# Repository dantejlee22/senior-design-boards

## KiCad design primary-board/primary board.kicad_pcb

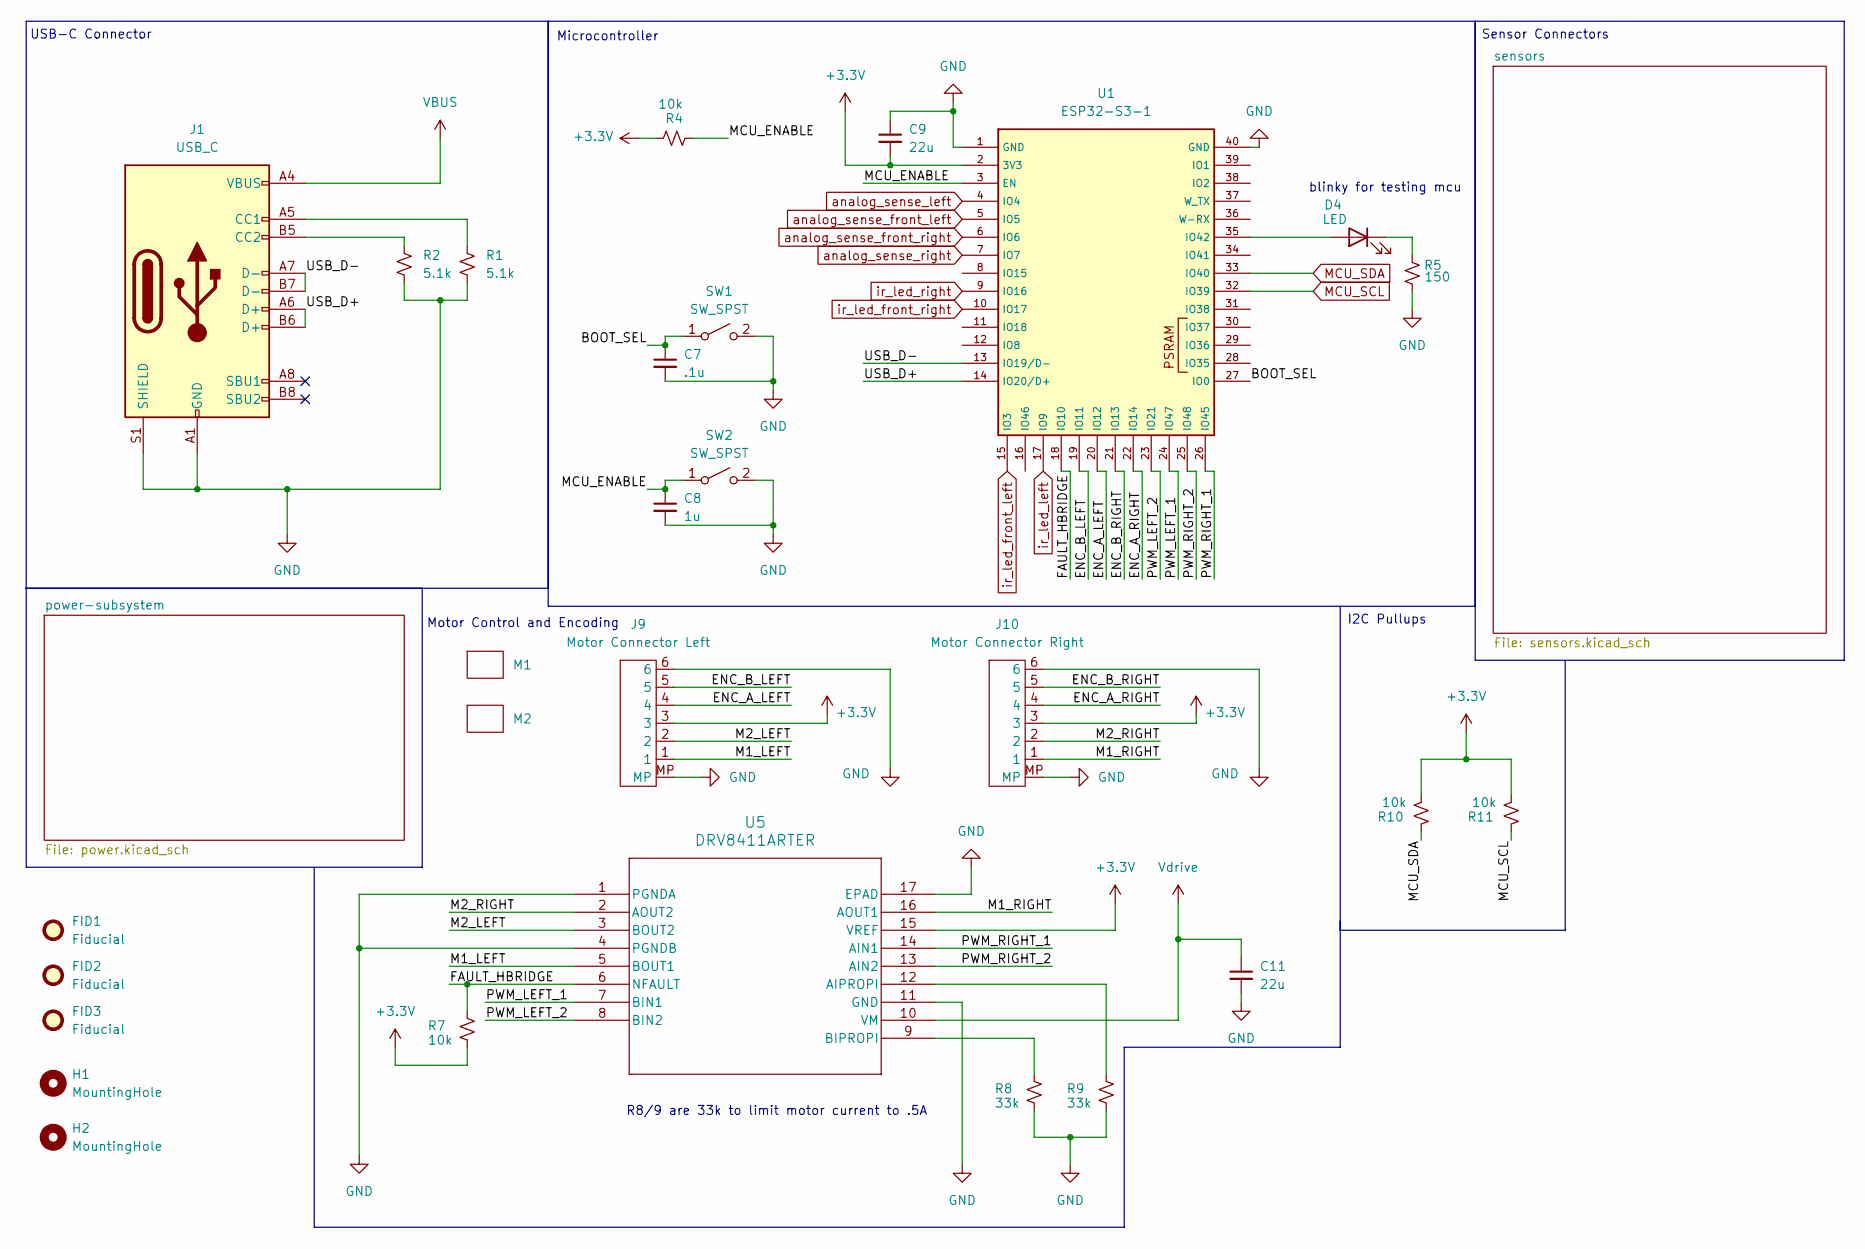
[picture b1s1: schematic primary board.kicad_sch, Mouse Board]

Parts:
C7: .1u; C_0603_1608Metric
C8: 1u; C_0603_1608Metric
C9, C11: 22u; C_0805_2012Metric
D4: LED; LED_0603_1608Metric
FID1, FID2, FID3: Fiducial; Fiducial_0.5mm_Mask1mm
H1, H2: MountingHole; MountingHole_2.2mm_M2
J1: USB_C; USB_C_Receptacle_GCT_USB4105-xx-A_16P_TopMnt_Horizontal
J9: Motor Connector Left; JST_SH_6_V
J10: Motor Connector Right; JST_SH_6_V
M1, M2: gearmotorenc
R1, R2: 5.1k; R_0603_1608Metric
R4, R7, R10, R11: 10k; R_0603_1608Metric
R5: 150; R_0603_1608Metric
R8, R9: 33k; R_0603_1608Metric_Pad0.98x0.95mm_HandSolder
SW1, SW2: SW_SPST; SW_SPST_Omron_B3FS-101xP
U1: ESP32-S3-1; ESP32-S3-1-WROOM_1
U5: DRV8411ARTER; WQFN16_RTE_TEX

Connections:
+3.3V: C9.2, J9.3, J10.3, R4.2, R7.2, R10.2, R11.2, U1.2 (3V3), U5.15 (VREF); also elsewhere on the board
/BOOT_SEL: C7.1, SW1.1 (A), U1.27 (IO0)
/ENC_A_LEFT: J9.4, U1.20 (IO12)
/ENC_A_RIGHT: J10.4, U1.22 (IO14)
/ENC_B_LEFT: J9.5, U1.19 (IO11)
/ENC_B_RIGHT: J10.5, U1.21 (IO13)
/FAULT_HBRIDGE: R7.1, U1.18 (IO10), U5.6 (NFAULT)
/M1_LEFT: J9.1, U5.5 (BOUT1)
/M1_RIGHT: J10.1, U5.16 (AOUT1)
/M2_LEFT: J9.2, U5.3 (BOUT2)
/M2_RIGHT: J10.2, U5.2 (AOUT2)
/MCU_ENABLE: C8.1, R4.1, SW2.1 (A), U1.3 (EN)
/PWM_LEFT_1: U1.24 (IO47), U5.7 (BIN1)
/PWM_LEFT_2: U1.23 (IO21), U5.8 (BIN2)
/PWM_RIGHT_1: U1.26 (IO45), U5.14 (AIN1)
/PWM_RIGHT_2: U1.25 (IO48), U5.13 (AIN2)
/USB_D+: J1.A6 (D+), J1.B6 (D+), U1.14 (IO20/D+)
/USB_D-: J1.A7 (D-), J1.B7 (D-), U1.13 (IO19/D-)
GND: C7.2, C8.2, C9.1, C11.2, J1.A1 (GND), J1.A12 (GND), J1.B1 (GND), J1.B12 (GND), J1.S1 (SHIELD), J9.6, J9.MP, J10.6, J10.MP, R1.1, R2.1, R5.1, R8.2, R9.2, SW1.2 (B), SW2.2 (B), U1.1 (GND), U1.40 (GND), U1.41 (GND__1), U5.1 (PGNDA), U5.4 (PGNDB), U5.11 (GND), U5.17 (EPAD); also elsewhere on the board
MCU_SCL: R11.1, U1.32 (IO39); also elsewhere on the board
MCU_SDA: R10.1, U1.33 (IO40); also elsewhere on the board
unnamed: D4.2 (A), U1.35 (IO42)
unnamed: D4.1 (K), R5.2
unnamed: J1.A5 (CC1), R1.2
unnamed: J1.B5 (CC2), R2.2
unnamed: R9.1, U5.12 (AIPROPI)
unnamed: R8.1, U5.9 (BIPROPI)
VBUS: J1.A4 (VBUS), J1.A9 (VBUS), J1.B4 (VBUS), J1.B9 (VBUS); also elsewhere on the board
Vdrive: C11.1, U5.10 (VM)
analog_sense_front_left: U1.5 (IO5); also elsewhere on the board
analog_sense_front_right: U1.6 (IO6); also elsewhere on the board
analog_sense_left: U1.4 (IO4); also elsewhere on the board
analog_sense_right: U1.7 (IO7); also elsewhere on the board
ir_led_front_left: U1.15 (IO3); also elsewhere on the board
ir_led_front_right: U1.10 (IO17); also elsewhere on the board
ir_led_left: U1.17 (IO9); also elsewhere on the board
ir_led_right: U1.9 (IO16); also elsewhere on the board

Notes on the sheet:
blinky for testing mcu
I2C Pullups
Motor Control and Encoding
USB-C Connector
Sensor Connectors
Microcontroller
R8/9 are 33k to limit motor current to .5A

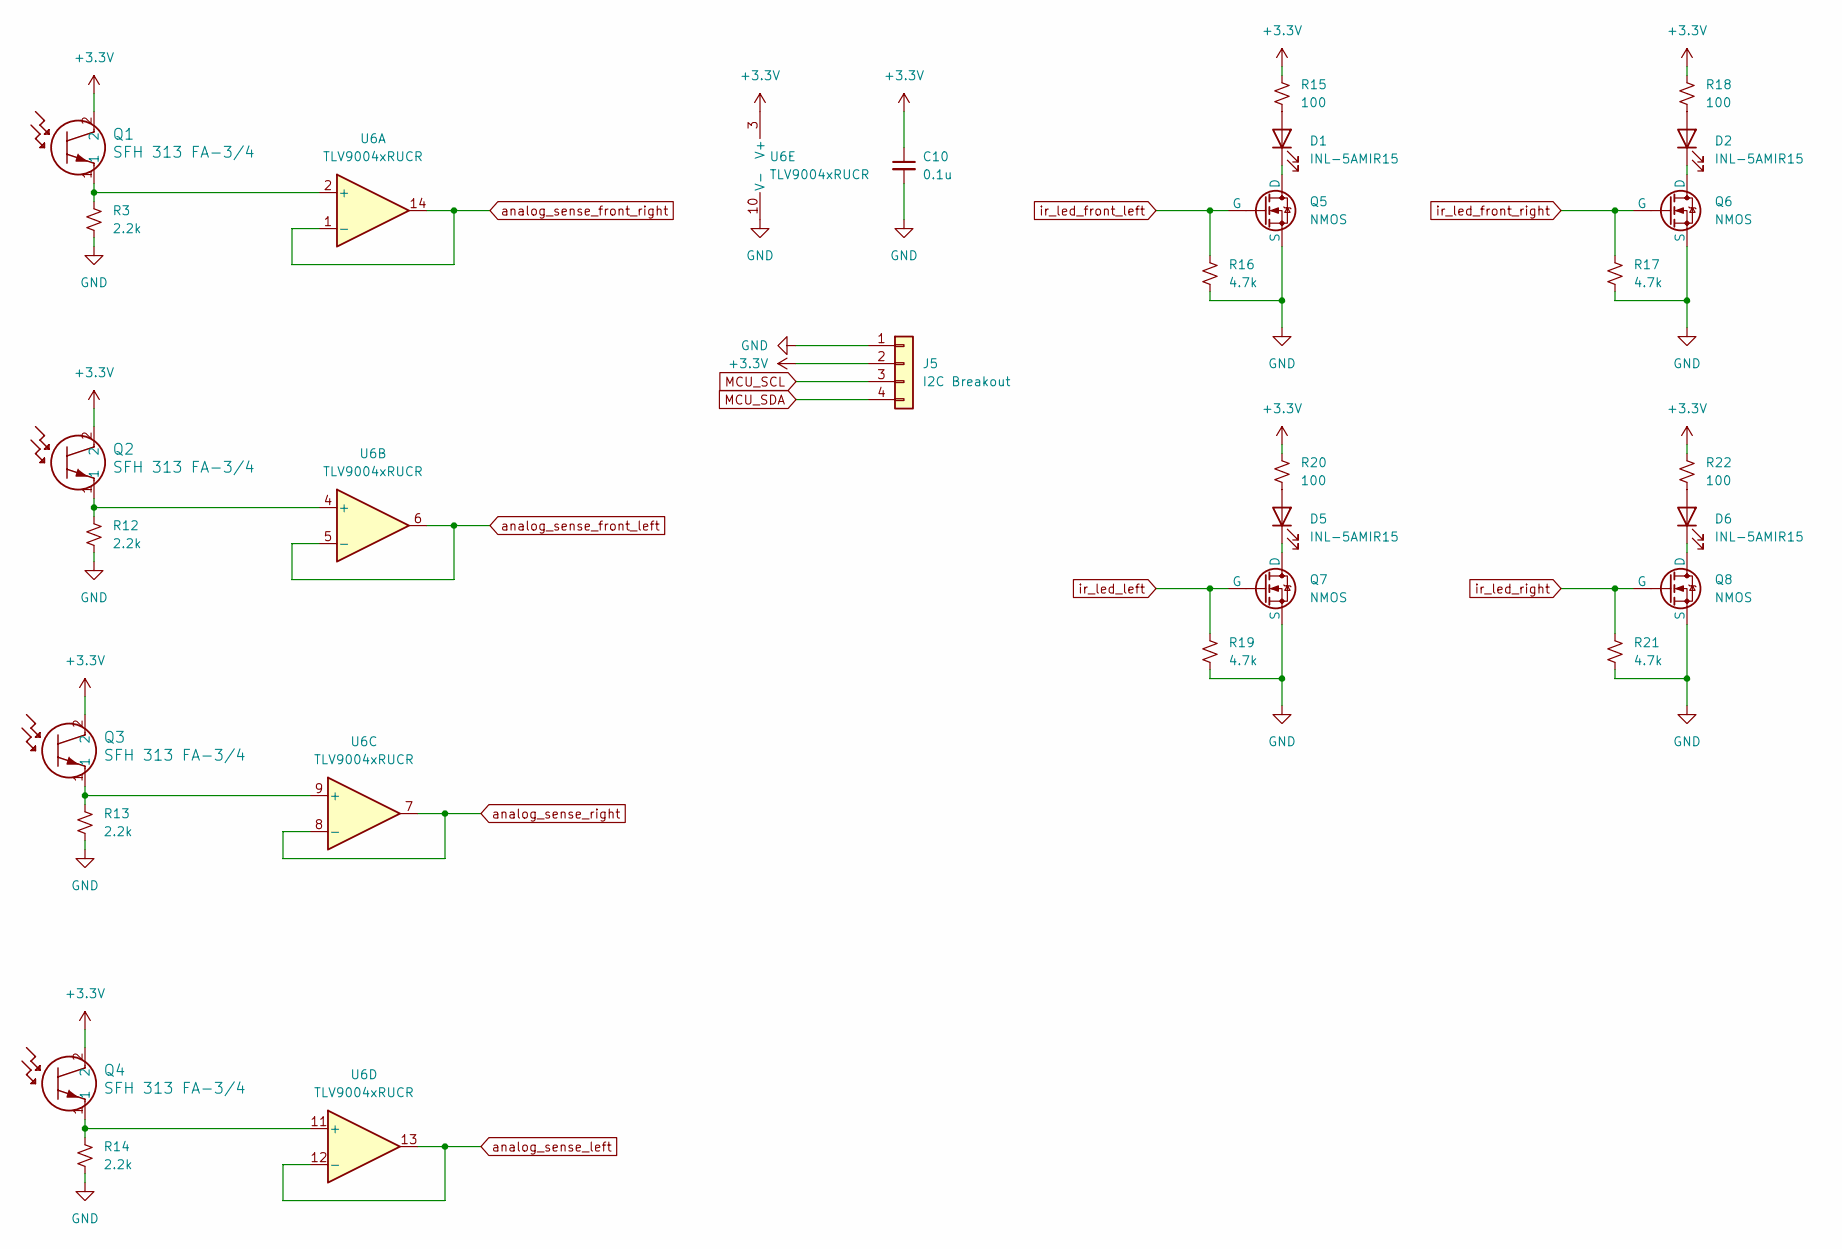
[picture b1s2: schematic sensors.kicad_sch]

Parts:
C10: 0.1u; C_0603_1608Metric
D1, D2, D5, D6: INL-5AMIR15; LED_D5.0mm_IRGrey
J5: I2C Breakout; PinSocket_1x04_P2.54mm_Vertical
Q1, Q2, Q3, Q4: SFH 313 FA-3/4; LED_D5.0mm_IRGrey
Q5, Q6, Q7, Q8: NMOS; SOT-23-3
R3, R12, R13, R14: 2.2k; R_0603_1608Metric
R15, R18, R20, R22: 100; R_0603_1608Metric
R16, R17, R19, R21: 4.7k; R_0603_1608Metric
U6: TLV9004xRUCR; Texas_S-PX2QFN-14

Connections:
+3.3V: C10.1, J5.2, Q1.2, Q2.2, Q3.2, Q4.2, R15.1, R18.1, R20.1, R22.1, U6.3 (V+); also elsewhere on the board
GND: C10.2, J5.1, Q5.3 (S), Q6.3 (S), Q7.3 (S), Q8.3 (S), R3.2, R12.2, R13.2, R14.2, R16.2, R17.2, R19.2, R21.2, U6.10 (V-); also elsewhere on the board
MCU_SCL: J5.3; also elsewhere on the board
MCU_SDA: J5.4; also elsewhere on the board
unnamed: D1.2 (A), R15.2
unnamed: D1.1 (K), Q5.1 (D)
unnamed: D2.2 (A), R18.2
unnamed: D2.1 (K), Q6.1 (D)
unnamed: D5.2 (A), R20.2
unnamed: D5.1 (K), Q7.1 (D)
unnamed: D6.2 (A), R22.2
unnamed: D6.1 (K), Q8.1 (D)
unnamed: Q1.1, R3.1, U6.2 (+)
unnamed: Q2.1, R12.1, U6.4 (+)
unnamed: Q3.1, R13.1, U6.9 (+)
unnamed: Q4.1, R14.1, U6.11 (+)
analog_sense_front_left: U6.5 (-), U6.6; also elsewhere on the board
analog_sense_front_right: U6.1 (-), U6.14; also elsewhere on the board
analog_sense_left: U6.12 (-), U6.13; also elsewhere on the board
analog_sense_right: U6.7, U6.8 (-); also elsewhere on the board
ir_led_front_left: Q5.2 (G), R16.1; also elsewhere on the board
ir_led_front_right: Q6.2 (G), R17.1; also elsewhere on the board
ir_led_left: Q7.2 (G), R19.1; also elsewhere on the board
ir_led_right: Q8.2 (G), R21.1; also elsewhere on the board

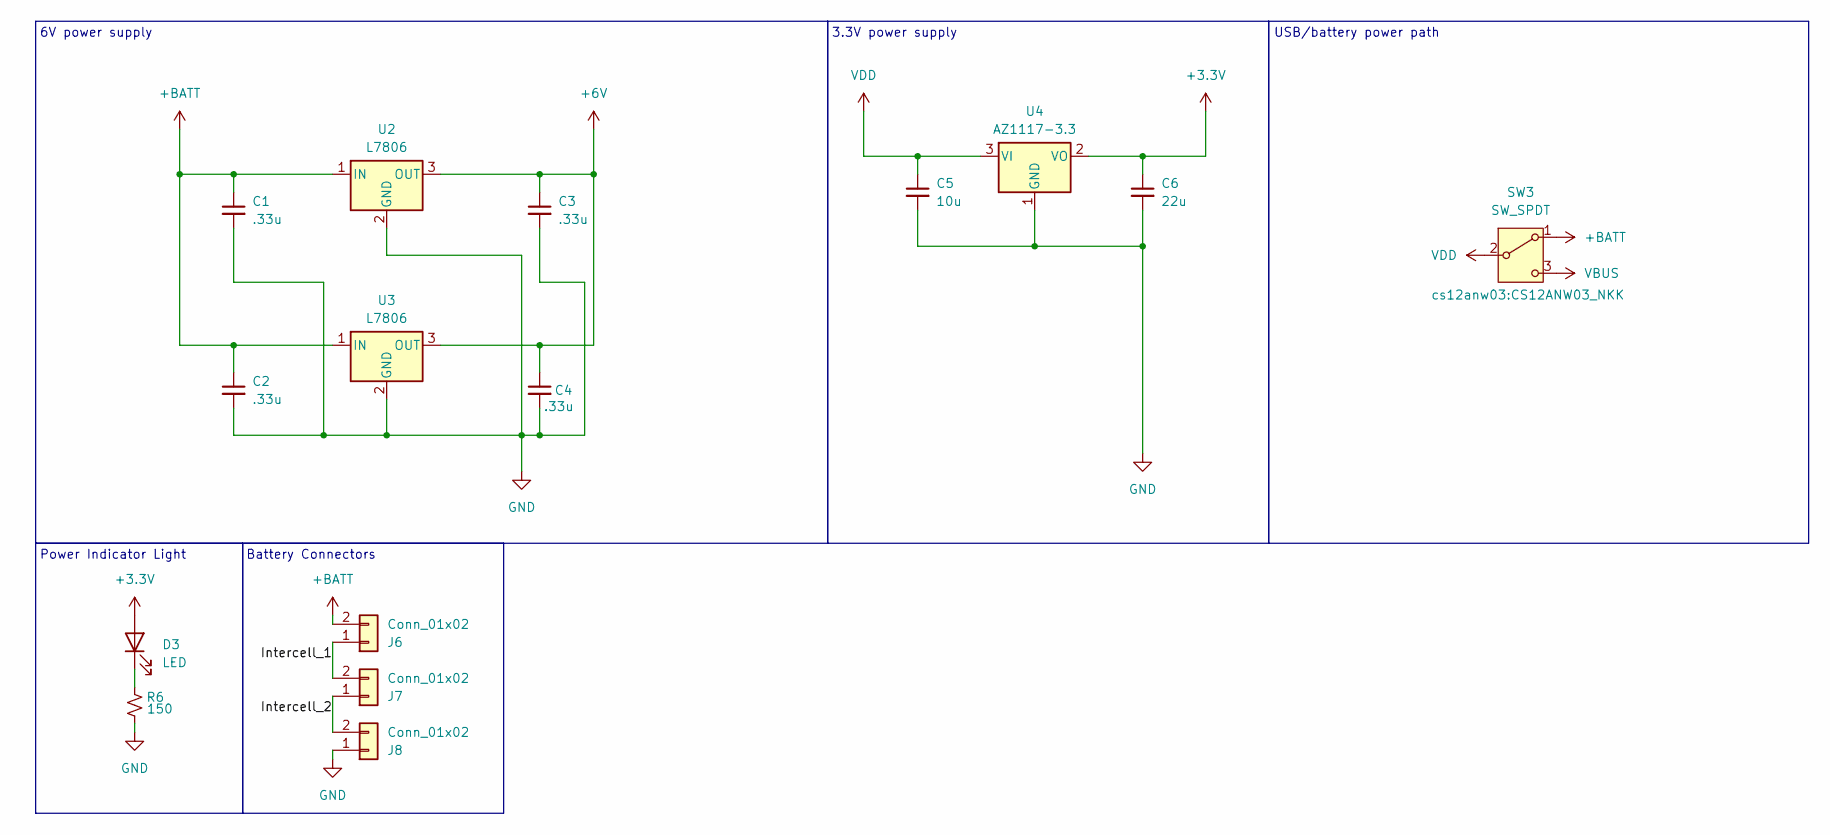
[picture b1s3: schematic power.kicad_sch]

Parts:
C1, C2, C3, C4: .33u; C_0603_1608Metric
C5: 10u; C_0805_2012Metric
C6: 22u; C_0805_2012Metric
D3: LED; LED_0603_1608Metric
J6, J7, J8: Conn_01x02; JST_PH_B2B-PH-K_1x02_P2.00mm_Vertical
R6: 150; R_0603_1608Metric
SW3: SW_SPDT; CS12ANW03_NKK
U2, U3: L7806; TO-263-2
U4: AZ1117-3.3; SOT-223-3_TabPin2

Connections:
+3.3V: C6.1, D3.2 (A), U4.2 (VO); also elsewhere on the board
+6V: C3.1, C4.1, U2.3 (OUT), U3.3 (OUT)
+BATT: C1.1, C2.1, J6.2, SW3.1 (A), U2.1 (IN), U3.1 (IN)
/power-subsystem/Intercell_1: J6.1, J7.2
/power-subsystem/Intercell_2: J7.1, J8.2
GND: C1.2, C2.2, C3.2, C4.2, C5.2, C6.2, J8.1, R6.1, U2.2 (GND), U3.2 (GND), U4.1 (GND); also elsewhere on the board
unnamed: D3.1 (K), R6.2
VBUS: SW3.3 (C); also elsewhere on the board
VDD: C5.1, SW3.2 (B), U4.3 (VI)

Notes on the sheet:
3.3V power supply
USB/battery power path
Battery Connectors
Power Indicator Light
6V power supply

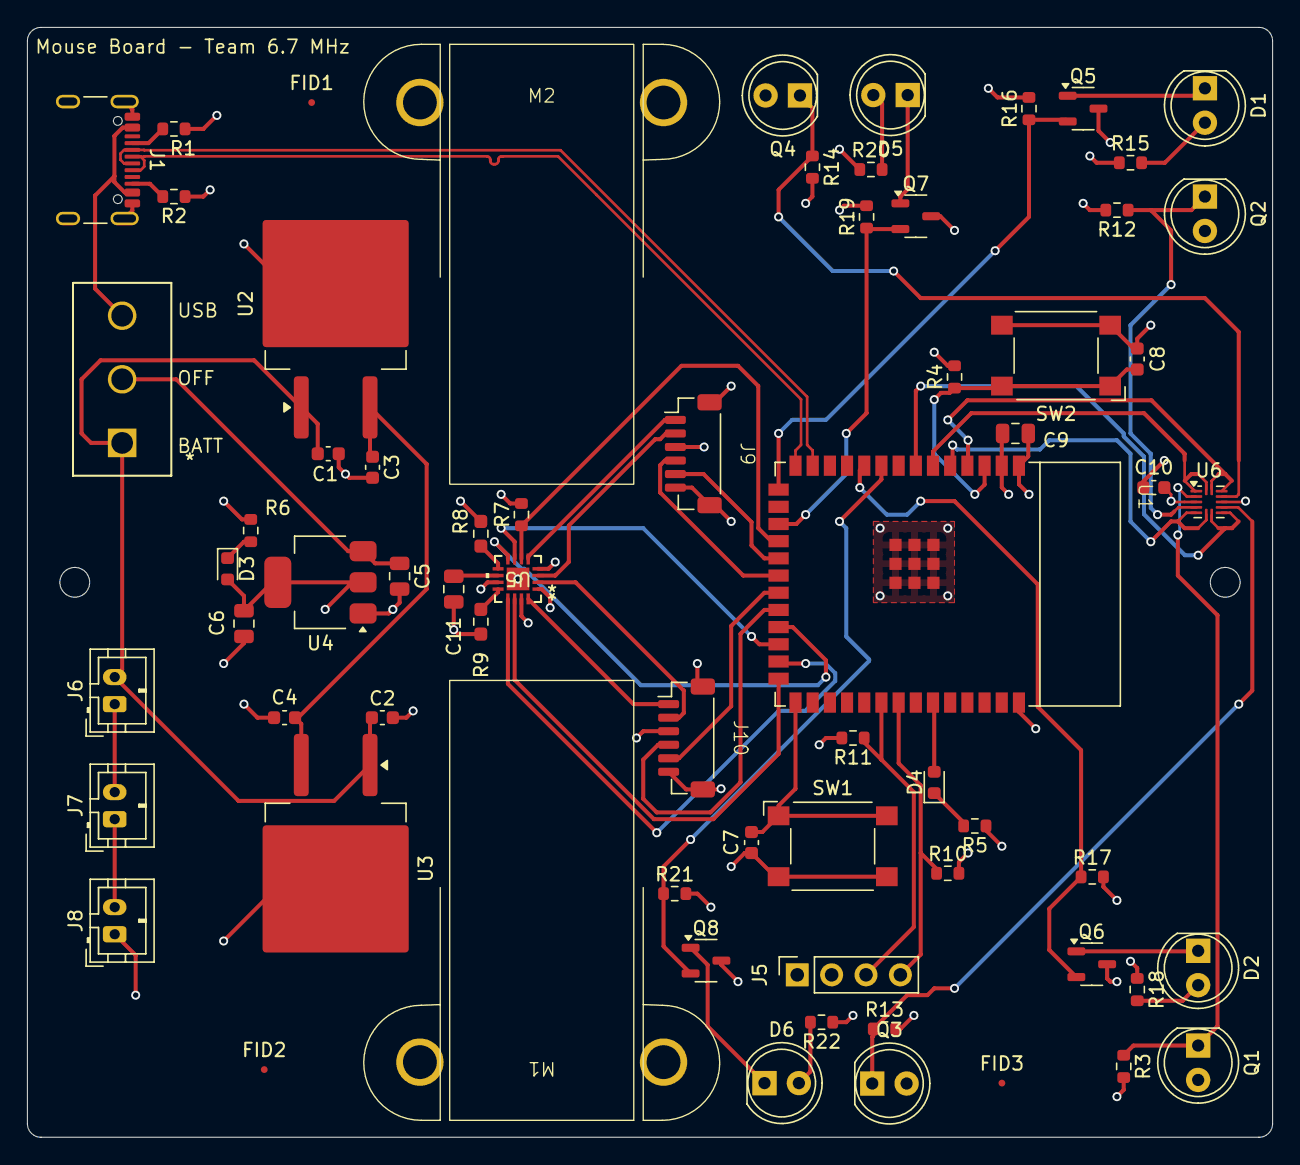
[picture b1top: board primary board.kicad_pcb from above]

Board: 4 copper layers, 92.0 x 82.0 mm, 70 parts (0 on the bottom side), 55 nets.

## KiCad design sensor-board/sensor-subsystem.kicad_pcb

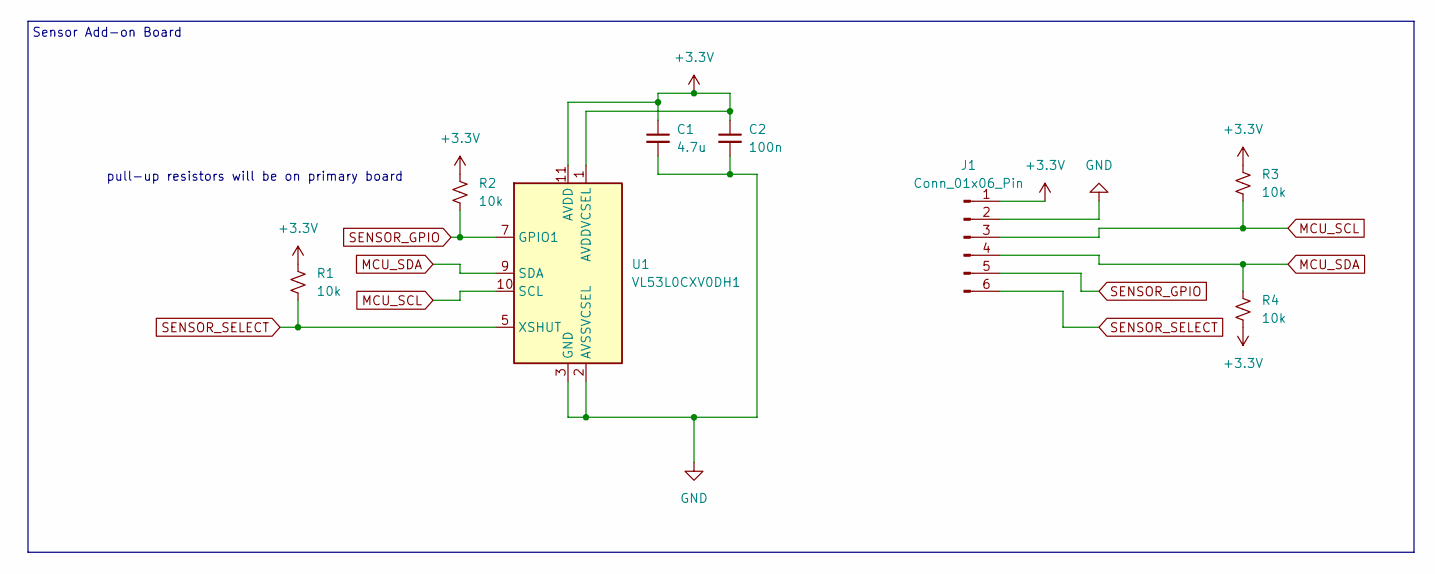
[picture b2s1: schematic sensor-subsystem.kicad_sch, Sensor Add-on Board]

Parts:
C1: 4.7u; C_0805_2012Metric
C2: 100n; C_0603_1608Metric
J1: Conn_01x06_Pin; PinHeader_1x06_P2.54mm_Horizontal
R1, R2, R3, R4: 10k; R_0805_2012Metric
U1: VL53L0CXV0DH1; ST_VL53L1x

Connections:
+3.3V: C1.1, C2.1, J1.1, R1.1, R2.1, R3.1, R4.2, U1.1 (AVDDVCSEL), U1.11 (AVDD)
GND: C1.2, C2.2, J1.2, U1.2 (AVSSVCSEL), U1.3 (GND), U1.4 (GND), U1.6 (GND), U1.12 (GND)
MCU_SCL: J1.3, R3.2, U1.10 (SCL)
MCU_SDA: J1.4, R4.1, U1.9 (SDA)
SENSOR_GPIO: J1.5, R2.2, U1.7 (GPIO1)
SENSOR_SELECT: J1.6, R1.2, U1.5 (XSHUT)

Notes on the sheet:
Sensor Add-on Board
pull-up resistors will be on primary board

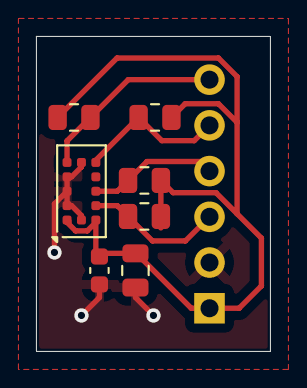
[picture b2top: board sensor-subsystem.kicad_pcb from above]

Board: 2 copper layers, 13.0 x 17.5 mm, 8 parts (1 on the bottom side), 6 nets.

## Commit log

2025-12-01 implemented feedback
2025-12-01 reorganized file tree swapped pushbuttons to smd
2025-12-02 improved sensor breakout board
2025-12-02 added motor connectors and h-bridge
2025-12-02 removed old lib
2025-12-02 complete board reroute. changed drv fault line into mcu. thickened all traces
2025-12-02 filleted board edges
2025-12-02 added via in pad thermal relief to drv
2025-12-04 adjusted via placement
2025-12-04 added i2c pullups
2025-12-04 adjusted drv8821 paste, added fiducials
2025-12-04 configured 3d models
2025-12-12 improved sensor board
2025-12-14 scrapped flawed power path, using a switch instead
2025-12-14 fixed 3d model for switch
2026-03-05 removed digital sensors
2026-03-07 analog work
2026-03-07 routed analog sensors
